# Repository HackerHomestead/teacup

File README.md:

# Tea Cup Tinker Board

The *Tea Cup* is a Tinker Board built on the *Ingenic T31* MIPS CPU, which is
specialised for Video & Audio Applications, and has highly integrated support
for multiple interfaces, LCD's, SD Card, Ethernet and more.

Designed with the community in mind, the *Tea Cup* is going to be ideal for
Kids, Tweens and Teens, and adults alike, to tinker with hardware and software
inside of an interface designed with ease-of-use and simplicity, but never 
locking the user down to a limited API or enviroment.

This project is currently in alpha, with a small team working on it, you can
join our [commuinty Discord Server](https://discord.gg/nxjvqgFQgJ)

----
## RevA Board Pictures

----
## Tools We Use
*All* of the work we are doing on Tea Cup, and any future projects are strictly
open-source only whenever possible, This means we do not distrubiute any CAD, 
Code, Docs, or any other files in any format that is not an open-source, Free or
FOSS Package, this is to ensure anyone can join development, and use our work in
their own endevours.

Having this in mind, the tools we are using in this project are:
* FreeCAD
* KiCad
* binwalk
* Ghidra
* GIMP

----
## Currently Working on:
* Getting an up-to-date SDK from ingenic
* Compiling uboot and attempting to create our own kernel with outdated SDK
* PCB Design for REV-A
* Testing differences between T31 Series and other Ingenic CPUs
* Finding a reliable and cheap method to get ICs from existing products
* Getting source for bulk order of T31's

## Have finished:
* REV-A Roadmap
* Compiled and ran code on the host device
* Reverse engineering of the "$1 webcam" PCB, with full Serial comms
* binwalk'd "$1 webcam" Firmware and working on Reverse Engineering
* Discord Server with management and co-ordination systems
* PCB Design and low volume boards for the first batch of REV-A prototypes

## Long Term TODO
* Check out the master [Teacup project board](https://github.com/users/HackerHomestead/projects/1/views/1)

## External links
* [Google Drive](https://drive.google.com/drive/u/1/folders/1BEhvPF5wQ0bi8qQTojf_yk7Au3pODrgF)
* [MIPS GCC Toolchain](https://drive.google.com/file/d/13-upgyvXytasOUA2UAwAwBOmOL2-lcfM/view)
* [Ingenic T31 Datasheet](https://drive.google.com/file/d/12MYs0BrT4tRH-UkWt7oT5_zm6LXiKhQJ/view)
* [Ingenic T31(ZX) SDK](https://github.com/HackerHomestead/Ingenic-SDK-T31-1.1.1-20200508)
* [Ingenic T31 Design Docs](https://drive.google.com/file/d/1u1oQInZgQonMenszIMkonlOMmzxKc2aA/view)

* [Hacker Homestead YouTube Channel](https://www.youtube.com/@hackerhomestead)
* [WLTechBlog](https://www.youtube.com/@wltechblog6330)
----
## Thanks
To everyone who has worked with us on Tea Cup, we thank you sincerely. It has
been, and will continue to be an honour working with you.

Thank you so much to the **core-dev** team for your continued work and effort 
with us on Tea Cup, without you this would have been impossible.  
* [HandyHacker](https://github.com/HackerHomestead)
* [CaptainRon](https://github.com/CapnRon)
* [BogdanTheGeek](https://github.com/BogdanTheGeek)

Thank you

## LICENCE
This project is under the GPL2.0 Licence. See LICENCE for more information.  
(c) 2023 HomesteadHacker

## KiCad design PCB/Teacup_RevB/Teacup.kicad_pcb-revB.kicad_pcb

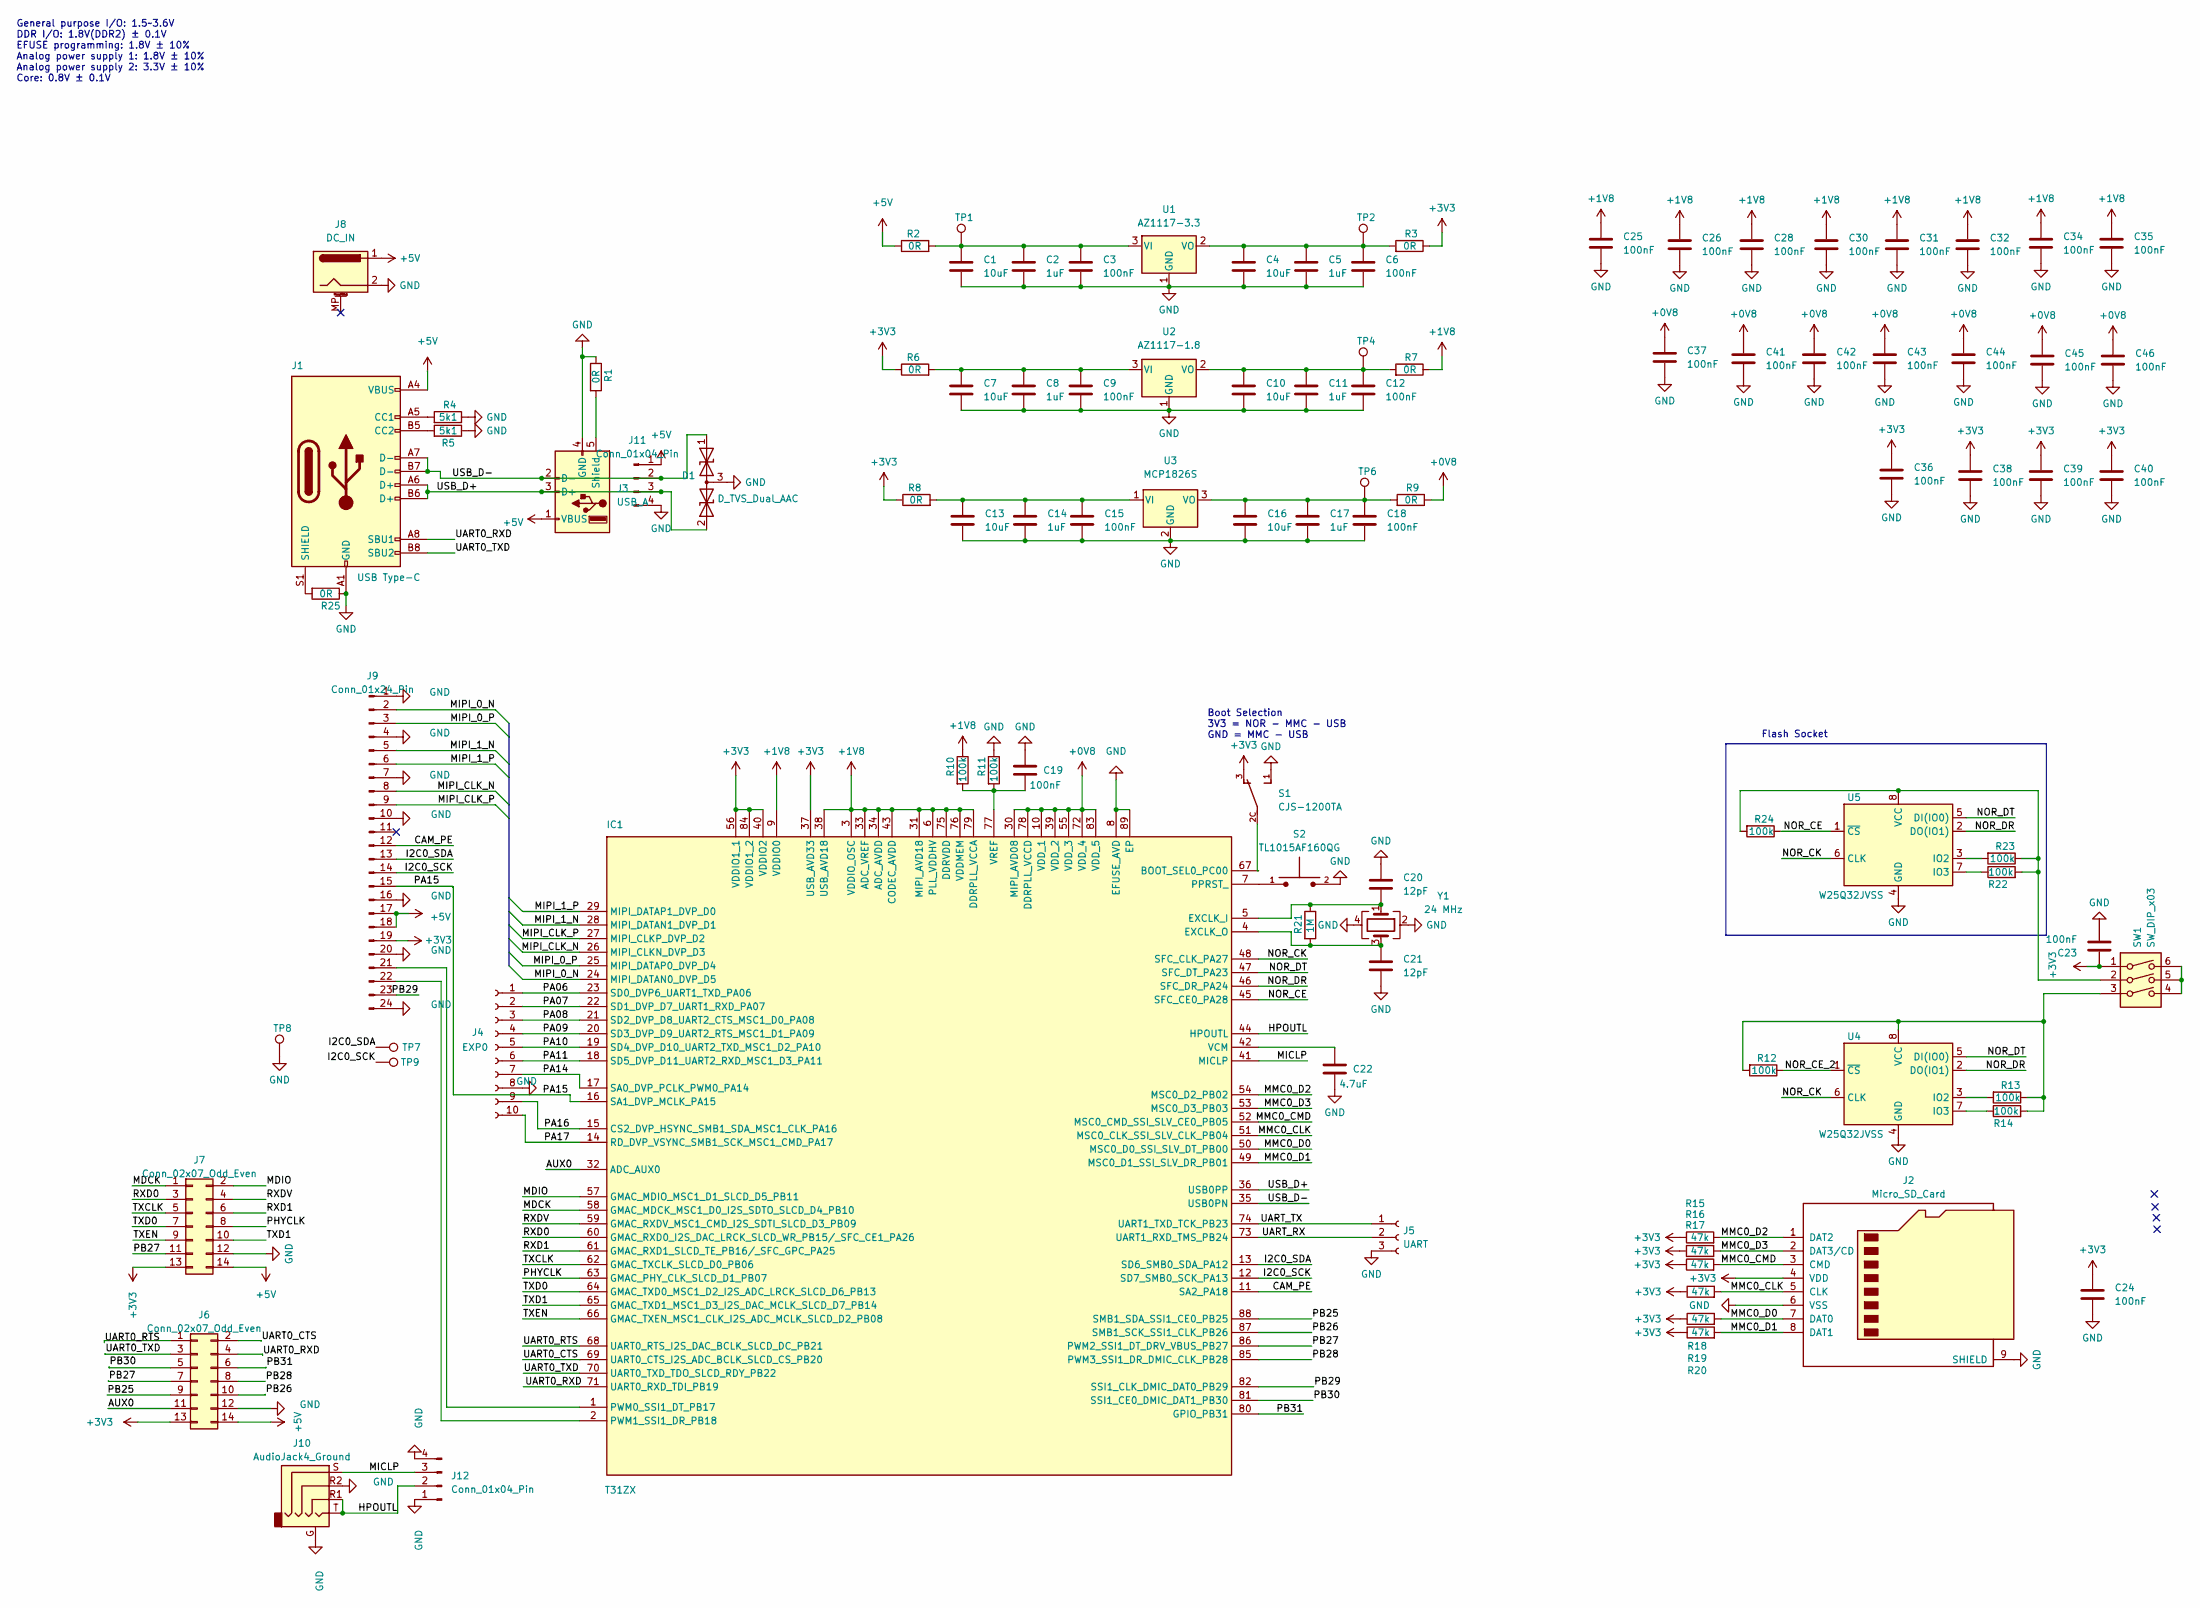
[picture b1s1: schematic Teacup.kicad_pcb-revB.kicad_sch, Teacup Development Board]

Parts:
C1, C4, C7, C10, C13, C16: 10uF; C_0805_2012Metric_Pad1.18x1.45mm_HandSolder
C2, C5, C8, C11, C14, C17: 1uF; C_0603_1608Metric_Pad1.08x0.95mm_HandSolder
C3, C6, C9, C12, C15, C18, C19: 100nF; C_0603_1608Metric_Pad1.08x0.95mm_HandSolder
C20, C21: 12pF; C_0402_1005Metric
C22: 4.7uF; C_0603_1608Metric_Pad1.08x0.95mm_HandSolder
C23, C24, C25, C26, C28, C30, C31, C32, C34, C35, C36, C37, C38, C39, C40, C41, C42, C43, C44, C45, C46: 100nF; C_0402_1005Metric
D1: D_TVS_Dual_AAC; SOT-323_SC-70; Manufacturer Part Number PESD5V0U2BT,215
IC1: T31ZX; QFN35P900X900X90-89N-D; Mouser Part Number 870-T31ZX
J1: USB Type-C; USB_C_Receptacle_HRO_TYPE-C-31-M-12; Manufacturer Part Number TYPE-C-31-M-12 (USB4105-GF-A)
J2: Micro_SD_Card; microSD_HC_Hirose_DM3D-SF
J3: USB_A; USB_A_TE_292303-7_Horizontal
J4: EXP0; PinHeader_1x10_P2.54mm_Vertical
J5: UART; PinHeader_1x03_P2.54mm_Vertical
J6, J7: Conn_02x07_Odd_Even; PinHeader_2x07_P2.54mm_Vertical
J8: DC_IN; BarrelJack_Wuerth_6941xx301002
J9: Conn_01x24_Pin; 687124149022
J10: AudioJack4_Ground; Jack_3.5mm_PJ320D_Horizontal
J11, J12: Conn_01x04_Pin; PinHeader_1x04_P2.54mm_Vertical
R1, R2, R3, R6, R7, R8, R9, R25: 0R; R_0603_1608Metric_Pad0.98x0.95mm_HandSolder
R4, R5: 5k1; R_0603_1608Metric_Pad0.98x0.95mm_HandSolder
R10, R11, R12, R13, R14, R22, R23, R24: 100k; R_0603_1608Metric_Pad0.98x0.95mm_HandSolder
R15, R16, R17, R18, R19, R20: 47k; R_0603_1608Metric_Pad0.98x0.95mm_HandSolder
R21: 1M; R_0402_1005Metric
S1: CJS-1200TA
S2: TL1015AF160QG; SW_TL1015AF160QG; PARTREV F
SW1: SW_DIP_x03; SW_DIP_SPSTx03_Slide_KingTek_DSHP03TJ_W5.25mm_P1.27mm_JPin
TP1, TP2, TP4, TP6, TP7, TP8, TP9: TestPoint; TestPoint_Pad_D1.5mm
U1: AZ1117-3.3; SOT-223-3_TabPin2; Manufacturer Part Number AZ1117IH-3.3TRG1
U2: AZ1117-1.8; SOT-223-3_TabPin2; Manufacturer Part Number AZ1117(CH)-1.8
U3: MCP1826S; SOT-223-3_TabPin2; Manufacturer Part Number MCP1826S
U4: W25Q32JVSS; SOIC-8_5.23x5.23mm_P1.27mm; Manufacturer Part Number W25Q32JVSS
U5: W25Q32JVSS; DIP-8_W7.62mm_Socket_LongPads
Y1: 24 MHz; Crystal_SMD_2016-4Pin_2.0x1.6mm; Manufacturer Part Number NX2016SA-24MHZ-EXS00A-CS07553

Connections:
+0V8: C37.1, C41.1, C42.1, C43.1, C44.1, C45.1, C46.1, IC1.10 (VDD_1), IC1.30 (MIPI_AVD08), IC1.39 (VDD_2), IC1.55 (VDD_3), IC1.72 (VDD_4), IC1.78 (DDRPLL_VCCD), IC1.83 (VDD_5), R9.1
+1V8: C25.1, C26.1, C28.1, C30.1, C31.1, C32.1, C34.1, C35.1, IC1.3 (VDDIO_OSC), IC1.6 (PLL_VDDHV), IC1.9 (VDDIO0), IC1.31 (MIPI_AVD18), IC1.33 (ADC_VREF), IC1.34 (ADC_AVDD), IC1.38 (USB_AVD18), IC1.43 (CODEC_AVDD), IC1.75 (DDRVDD), IC1.76 (VDDMEM), IC1.79 (DDRPLL_VCCA), R7.1, R10.1
+3V3: C23.1, C24.1, C36.1, C38.1, C39.1, C40.1, IC1.37 (USB_AVD33), IC1.40 (VDDIO2), IC1.56 (VDDIO1_1), IC1.84 (VDDIO1_2), J2.4 (VDD), J6.13, J7.13, J9.19, R3.1, R6.1, R8.1, R15.1, R16.1, R17.1, R18.1, R19.1, R20.1, S1.3, SW1.1
+5V: J1.A4 (VBUS), J1.A9 (VBUS), J1.B4 (VBUS), J1.B9 (VBUS), J3.1 (VBUS), J6.14, J7.14, J8.1, J9.17, J9.18, J11.1, R2.1
/AUX0: IC1.32 (ADC_AUX0), J6.11
/CAM_PE: IC1.11 (SA2_PA18), J9.12
/HPOUTL: IC1.44 (HPOUTL), J10.R1, J10.T, J12.2
/I2C0_SCK: IC1.12 (SD7_SMB0_SCK_PA13), J9.14, TP9.1
/I2C0_SDA: IC1.13 (SD6_SMB0_SDA_PA12), J9.13, TP7.1
/MDCK: IC1.58 (GMAC_MDCK_MSC1_D0_I2S_SDTO_SLCD_D4_PB10), J7.1
/MDIO: IC1.57 (GMAC_MDIO_MSC1_D1_SLCD_D5_PB11), J7.2
/MICLP: IC1.41 (MICLP), J10.S, J12.3
/MIPI_0_N: IC1.24 (MIPI_DATAN0_DVP_D5), J9.2
/MIPI_0_P: IC1.25 (MIPI_DATAP0_DVP_D4), J9.3
/MIPI_1_N: IC1.28 (MIPI_DATAN1_DVP_D1), J9.5
/MIPI_1_P: IC1.29 (MIPI_DATAP1_DVP_D0), J9.6
/MIPI_CLK_N: IC1.26 (MIPI_CLKN_DVP_D3), J9.8
/MIPI_CLK_P: IC1.27 (MIPI_CLKP_DVP_D2), J9.9
/MMC0_CLK: IC1.51 (MSC0_CLK_SSI_SLV_CLK_PB04), J2.5 (CLK), R18.2
/MMC0_CMD: IC1.52 (MSC0_CMD_SSI_SLV_CE0_PB05), J2.3 (CMD), R17.2
/MMC0_D0: IC1.50 (MSC0_D0_SSI_SLV_DT_PB00), J2.7 (DAT0), R19.2
/MMC0_D1: IC1.49 (MSC0_D1_SSI_SLV_DR_PB01), J2.8 (DAT1), R20.2
/MMC0_D2: IC1.54 (MSC0_D2_PB02), J2.1 (DAT2), R15.2
/MMC0_D3: IC1.53 (MSC0_D3_PB03), J2.2 (DAT3/CD), R16.2
/NOR_CE: IC1.45 (SFC_CE0_PA28), R24.1, U5.1 (~CS)
/NOR_CE_2: R12.1, U4.1 (~CS)
/NOR_CK: IC1.48 (SFC_CLK_PA27), U4.6 (CLK), U5.6 (CLK)
/NOR_DR: IC1.46 (SFC_DR_PA24), U4.2 (DO(IO1)), U5.2 (DO(IO1))
/NOR_DT: IC1.47 (SFC_DT_PA23), U4.5 (DI(IO0)), U5.5 (DI(IO0))
/PA06: IC1.23 (SD0_DVP6_UART1_TXD_PA06), J4.1
/PA07: IC1.22 (SD1_DVP_D7_UART1_RXD_PA07), J4.2
/PA08: IC1.21 (SD2_DVP_D8_UART2_CTS_MSC1_D0_PA08), J4.3
/PA09: IC1.20 (SD3_DVP_D9_UART2_RTS_MSC1_D1_PA09), J4.4
/PA10: IC1.19 (SD4_DVP_D10_UART2_TXD_MSC1_D2_PA10), J4.5
/PA11: IC1.18 (SD5_DVP_D11_UART2_RXD_MSC1_D3_PA11), J4.6
/PA14: IC1.17 (SA0_DVP_PCLK_PWM0_PA14), J4.7
/PA15: IC1.16 (SA1_DVP_MCLK_PA15), J9.15
/PA16: IC1.15 (CS2_DVP_HSYNC_SMB1_SDA_MSC1_CLK_PA16), J4.9
/PA17: IC1.14 (RD_DVP_VSYNC_SMB1_SCK_MSC1_CMD_PA17), J4.10
/PB25: IC1.88 (SMB1_SDA_SSI1_CE0_PB25), J6.9
/PB26: IC1.87 (SMB1_SCK_SSI1_CLK_PB26), J6.10
/PB27: IC1.86 (PWM2_SSI1_DT_DRV_VBUS_PB27), J6.7, J7.11
/PB28: IC1.85 (PWM3_SSI1_DR_DMIC_CLK_PB28), J6.8
/PB29: IC1.82 (SSI1_CLK_DMIC_DAT0_PB29), J9.23
/PB30: IC1.81 (SSI1_CE0_DMIC_DAT1_PB30), J6.5
/PB31: IC1.80 (GPIO_PB31), J6.6
/PHYCLK: IC1.63 (GMAC_PHY_CLK_SLCD_D1_PB07), J7.8
/RXD0: IC1.60 (GMAC_RXD0_I2S_DAC_LRCK_SLCD_WR_PB15/_SF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), J7.3
/RXD1: IC1.61 (GMAC_RXD1_SLCD_TE_PB16/_SFC_GPC_PA25), J7.6
/RXDV: IC1.59 (GMAC_RXDV_MSC1_CMD_I2S_SDTI_SLCD_D3_PB09), J7.4
/TXCLK: IC1.62 (GMAC_TXCLK_SLCD_D0_PB06), J7.5
/TXD0: IC1.64 (GMAC_TXD0_MSC1_D2_I2S_ADC_LRCK_SLCD_D6_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), J7.7
/TXD1: IC1.65 (GMAC_TXD1_MSC1_D3_I2S_DAC_MCLK_SLCD_D7_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), J7.10
/TXEN: IC1.66 (GMAC_TXEN_MSC1_CLK_I2S_ADC_MCLK_SLCD_D2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), J7.9
/UART0_CTS: IC1.69 (UART0_CTS_I2S_ADC_BCLK_SLCD_CS_PB20), J6.2
/UART0_RTS: IC1.68 (UART0_RTS_I2S_DAC_BCLK_SLCD_DC_PB21), J6.1
/UART0_RXD: IC1.71 (UART0_RXD_TDI_PB19), J1.A8 (SBU1), J6.4
/UART0_TXD: IC1.70 (UART0_TXD_TDO_SLCD_RDY_PB22), J1.B8 (SBU2), J6.3
/UART_RX: IC1.73 (UART1_RXD_TMS_PB24), J5.2
/UART_TX: IC1.74 (UART1_TXD_TCK_PB23), J5.1
/USB_D+: D1.2 (A2), IC1.36 (USB0PP), J1.A6 (D+), J1.B6 (D+), J3.3 (D+), J11.3
/USB_D-: D1.1 (A1), IC1.35 (USB0PN), J1.A7 (D-), J1.B7 (D-), J3.2 (D-), J11.2
GND: C1.2, C2.2, C3.2, C4.2, C5.2, C6.2, C7.2, C8.2, C9.2, C10.2, C11.2, C12.2, C13.2, C14.2, C15.2, C16.2, C17.2, C18.2, C19.1, C20.1, C21.2, C22.2, C23.2, C24.2, C25.2, C26.2, C28.2, C30.2, C31.2, C32.2, C34.2, C35.2, C36.2, C37.2, C38.2, C39.2, C40.2, C41.2, C42.2, C43.2, C44.2, C45.2, C46.2, D1.3 (common), IC1.8 (EFUSE_AVD), IC1.89 (EP), J1.A1 (GND), J1.A12 (GND), J1.B1 (GND), J1.B12 (GND), J2.6 (VSS), J2.9 (SHIELD), J3.4 (GND), J4.8, J5.3, J6.12, J7.12, J8.2, J9.1, J9.4, J9.7, J9.10, J9.16, J9.20, J9.24, J10.G, J10.R2, J11.4, J12.1, J12.4, R1.1, R4.1, R5.1, R11.1, R25.1, S1.1, S2.2, TP8.1, U1.1 (GND), U2.1 (GND), U3.2 (GND), U4.4 (GND), U5.4 (GND), Y1.2, Y1.4
unnamed: IC1.67 (BOOT_SEL0_PC00), S1.2C
unnamed: C20.2, IC1.5 (EXCLK_I), R21.1, Y1.1
unnamed: C21.1, IC1.4 (EXCLK_O), R21.2, Y1.3
unnamed: IC1.7 (PPRST_), S2.1
unnamed: IC1.1 (PWM0_SSI1_DT_PB17), J9.21
unnamed: IC1.2 (PWM1_SSI1_DR_PB18), J9.22
unnamed: C22.1, IC1.42 (VCM)
unnamed: C19.2, IC1.77 (VREF), R10.2, R11.2
unnamed: J1.A5 (CC1), R4.2
unnamed: J1.B5 (CC2), R5.2
unnamed: J1.S1 (SHIELD), R25.2
unnamed: J3.5 (Shield), R1.2
unnamed: SW1.4, SW1.5, SW1.6
unnamed: C1.1, C2.1, C3.1, R2.2, TP1.1, U1.3 (VI)
unnamed: C4.1, C5.1, C6.1, R3.2, TP2.1, U1.2 (VO)
unnamed: C7.1, C8.1, C9.1, R6.2, U2.3 (VI)
unnamed: C10.1, C11.1, C12.1, R7.2, TP4.1, U2.2 (VO)
unnamed: C13.1, C14.1, C15.1, R8.2, U3.1 (VI)
unnamed: C16.1, C17.1, C18.1, R9.2, TP6.1, U3.3 (VO)
unnamed: R13.2, U4.3 (IO2)
unnamed: R14.1, U4.7 (IO3)
unnamed: R12.2, R13.1, R14.2, SW1.3, U4.8 (VCC)
unnamed: R23.2, U5.3 (IO2)
unnamed: R22.1, U5.7 (IO3)
unnamed: R22.2, R23.1, R24.2, SW1.2, U5.8 (VCC)

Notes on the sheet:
Boot Selection 3V3 = NOR - MMC - USB GND = MMC - USB
Flash Socket
General purpose I/O: 1.5~3.6V DDR I/O: 1.8V(DDR2) ± 0.1V EFUSE programming: 1.8V ± 10% Analog power supply 1: 1.8V ± 10% Analog power supply 2: 3.3V ± 10% Core: 0.8V ± 0.1V

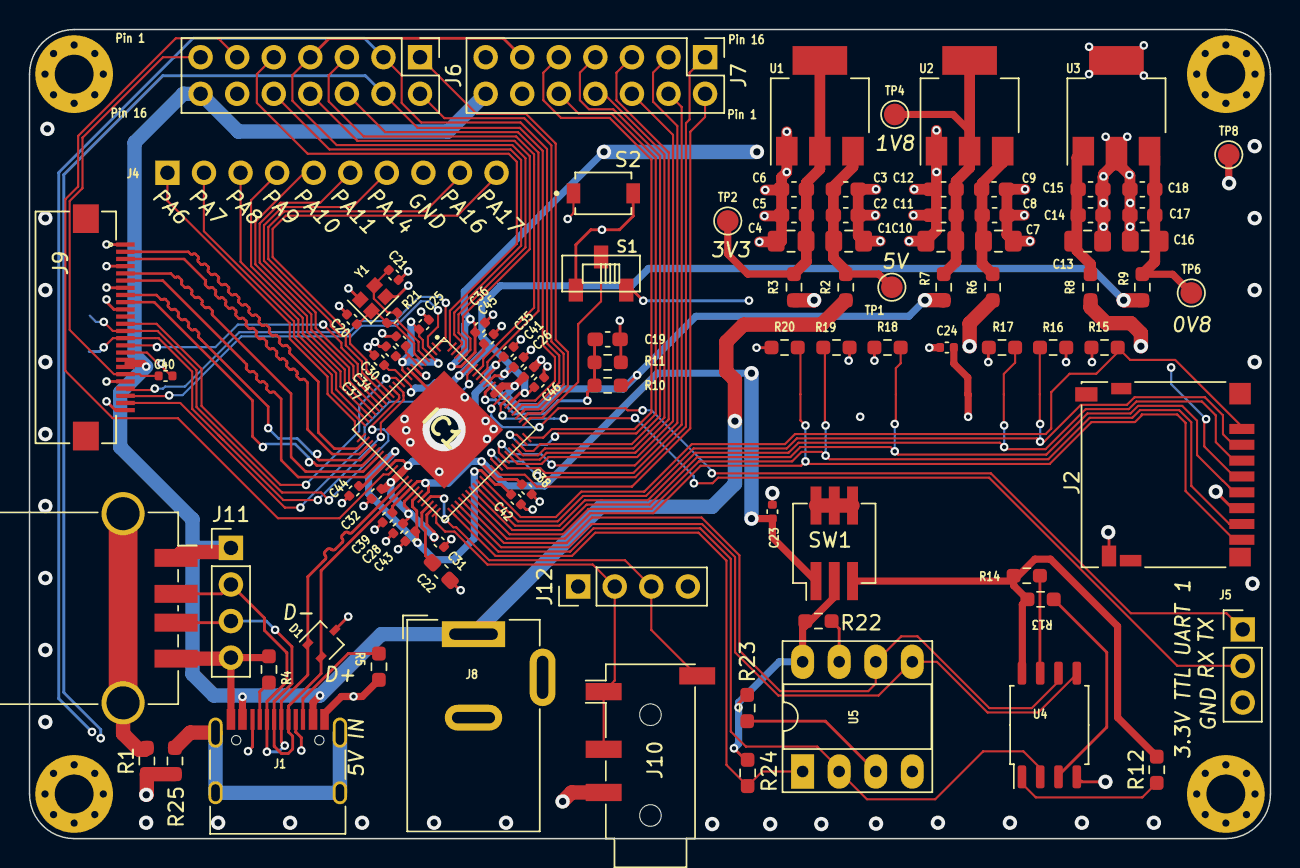
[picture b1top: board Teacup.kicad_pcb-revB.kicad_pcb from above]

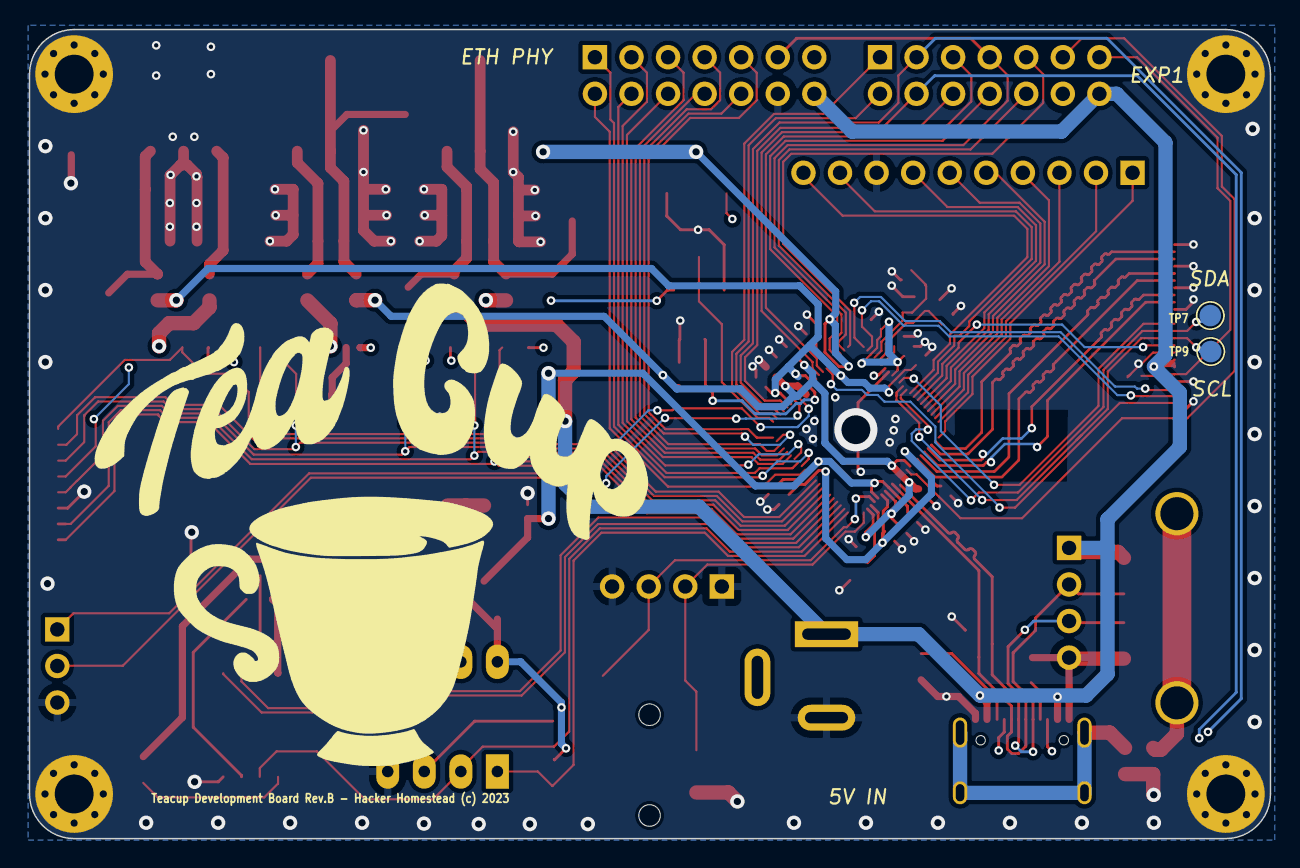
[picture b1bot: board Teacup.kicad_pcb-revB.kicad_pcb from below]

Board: 4 copper layers, 86.2 x 56.2 mm, 98 parts (2 on the bottom side), 88 nets.

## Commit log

2023-03-24 initial comit
2023-03-24 pcb: symbols and footprints
2023-03-24 pcb: teacup: project files
2023-03-24 Docs links
2023-03-25 pcb: sym: cleanup and order
2023-03-25 Documentation go vrr
2023-03-25 pcb: pow + clock + usb
2023-03-25 pcb: regulators
2023-03-25 pcb: flash + footprints
2023-03-26 Artwork :)
2023-03-26 banner
2023-03-26 toolkit link
2023-03-28 pcb: sch done, initial placement
2023-03-30 pcb: routed high speed signals
2023-03-31 pcb: routing done
2023-03-31 mips64aws tests
2023-04-01 pcb: boms and gerbers
2023-04-13 RevA Commit
2023-04-13 Submitted inital order
2023-04-17 Added Postion File
2023-05-01 Updated Readme and added some artwork
2023-05-01 Fixed image link
2023-05-13 Update README.md
    Add a "Done" item about RevA prototypes, to clarify existing boards are not RevA
2023-06-02 From Teacuo.kicad_pcb-revB-5-28-23-2217BST

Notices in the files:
PCB/Teacup_RevB/Teacup.kicad_pcb-revB.kicad_pcb:
${TITLE} Rev.${REVISION} - ${COMPANY} (c) 2023
